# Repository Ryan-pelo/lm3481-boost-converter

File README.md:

# lm3481-boost-converter
# Overview
This project started when I needed a small footprint boost converter for a single cell lithium ion battery. I couldn't find anything that could deliver the current I needed in a small form factor, so I created this project with the help of Texas Instrument's [Webench tool][1]. This boost topology uses the [LM3841][2] boost controller to step up from 3-4.2v to 5v with a theoretical max current of 10A (WIP). The board is designed with a small footprint measuring 1.5" x 0.72"(38mm x 18.5mm) and an overall height under 0.75". **This is a work in progress and is not finished.**

# Specs and Adjusting Functionality
The controller is versitile and can be easily altered to meet your own requirement specs. I'd advise using Webench for design, and refer to my schematic for a sample layout or use it as a starting point. 
## Vin
The Vin pin requires a minimum of 2.97v to function and a maximum of 48v. If you want to add an under-voltage lockout, see UVLO.
## UVLO
The under-voltage lockout pin forces the controller off if a minimum voltage (set by the user) at Vin is not met. The lockout voltage is determined by a voltage divider created by Rivp1 and Rivp2. More detail regarding how these values are determined can be found in 7.3.5 (p17) of the datasheet.
## Vout
The output voltage is determined by the voltage created by a resistor divider at the feedback pin. Resistors Rfb1 and Rfb2 serve to create the divider, while Rfb3 is a 500ohm trimpot for fine tuning the output. Info about how to choose the values of these resistors can be found in 8.2.1.2.3 (p22) of the datasheet.
## Current Limiting
The voltage drop across the Rsense resistor determines the max current. The value of this resistor can be found in 8.2.1.2.3 (p22) of the datasheet.
## Cin & Cout
To save space, height, and ESR, I opted to use banks of ceramic capacitors. Since I couldn't find any existing stacked MLCC arrays, I manually soldered two rows stacked on each other. On Kicad, their footprints are single 1206s, but the schematic has some exposed power rails to accomodate for capacitor arrays. High capacitance MLCCs are not available in higher voltages, so it may not work for all designs.
## Current Limiting on the Drive Pin
Although the datasheet does not mention any resistor at the mosfet gate, I found one necessary since I was seeing ringing. Anything from 10-30ohm cut down on the ringing for me.

[1]: https://webench.ti.com/power-designer/
[2]: https://www.ti.com/product/LM3481

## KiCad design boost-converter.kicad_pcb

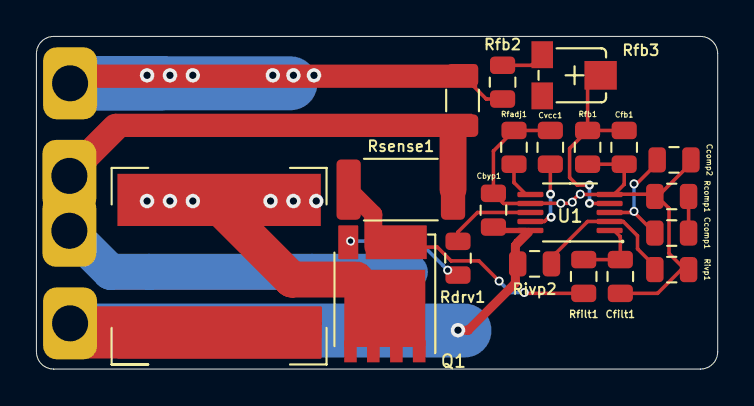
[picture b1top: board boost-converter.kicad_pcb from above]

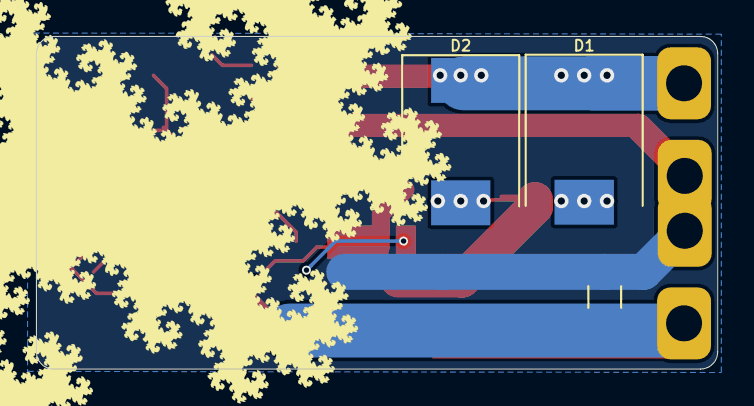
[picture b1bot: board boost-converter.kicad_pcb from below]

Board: 2 copper layers, 37.8 x 18.5 mm, 27 parts (3 on the bottom side), 15 nets.

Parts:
Cbyp1: 1uF; C_0805_2012Metric
Ccomp1: 68nF; C_0805_2012Metric
Ccomp2: 3.3nF; C_0805_2012Metric
Cfb1: 100pF; R_0805_2012Metric
Cfilt1: 10pf; C_0805_2012Metric
Cin1: 25x100uF; C_1206_3216Metric
Cout1: 100uF; C_1206_3216Metric
Cvcc1: 470nf; C_0805_2012Metric
D1, D2: D; D_SMC
L1: 1uH; XAL1010
Q1: 30V 100A; TDSON-8-1_HandSoldering
Rcomp1: 1.87kOhm; R_0805_2012Metric
Rdrv1: 30; R_0805_2012Metric
Rfadj1: 88kOhm; R_0805_2012Metric
Rfb1: 1kOhm; R_0805_2012Metric
Rfb2: 2.75k; R_0805_2012Metric
Rfb3: 500; tc33
Rfilt1: 100; R_0805_2012Metric
Rivp1: 45.3kOhm; R_0805_2012Metric
Rivp2: 44.2kOhm; R_0805_2012Metric
Rsense1: 2.45mOhm; R_2512_6332Metric
U1: LM3481; VSSOP-10_3x3mm_P0.5mm
Vin+1: MountingHole_Pad; Pad
Vin-1: MountingHole_Pad; Pad
Vout+1: MountingHole_Pad; Pad
Vout-1: MountingHole_Pad; Pad

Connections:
GND: Cbyp1.1, Ccomp2.2, Cfb1.1, Cfilt1.2, Cin1.2, Cout1.2, Cvcc1.2, Rcomp1.2, Rfadj1.2, Rfb1.2, Rivp1.2, Rsense1.2, U1.5, U1.7, Vin-1.1, Vout-1.1
unnamed: Ccomp1.1, Ccomp2.1, U1.3
unnamed: Ccomp1.2, Rcomp1.1
unnamed: Cfb1.2, Rfb1.1, Rfb3.2, U1.4
unnamed: Cfilt1.1, Rfilt1.1, U1.1
unnamed: Cout1.1, D1.1, D2.1, Rfb2.2, Vout+1.1
unnamed: Cvcc1.1, U1.9
unnamed: D1.2, D2.2, L1.2, Q1.5
unnamed: Q1.1, Q1.2, Q1.3, Rfilt1.2, Rsense1.1
unnamed: Q1.4, Rdrv1.1
unnamed: Rdrv1.2, U1.8
unnamed: Rfadj1.1, U1.6
unnamed: Rfb2.1, Rfb3.1
unnamed: Rivp1.1, Rivp2.2, U1.2
Vin: Cbyp1.2, Cin1.1, L1.1, Rivp2.1, U1.10, Vin+1.1

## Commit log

2020-10-11 Create LICENSE
